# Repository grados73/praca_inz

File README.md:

# Praca Dyplomowa (inżynierska)
Tematem pracy była Analiza konstrukcyjna systemu śledzenia linii.

Zaawansowane rozwiązania techniczne pomagają w osiąganiu coraz to lepszych wyników w różnych dyscyplinach sportowych,
towarzyszą podczas treningów zapewniając wsparcie i umożliwiając pokonywanie kolejnych granic oraz realizację założonych celów.
Wspierają one nie tylko zawodowych sportowców, ale również amatorów, ze względu na ich ogólną dostępność. 
Coraz częściej spotkać można bardzo zaawansowane aplikacje i urządzenia, wykorzystywane w sporcie, 
a oferta firm zajmujących się produkcją takiego sprzętu nieustannie się poszerza o nowe rozwiązania.

Celem pracy była realizacja robota, wykorzystującego system śledzenia linii, w celu utrzymywania zadanego tempa biegacza trenującego na bieżni lekkoatletycznej, 
aby osiągnąć większą efektywność treningów. Projekt składa się z dwóch podzespołów. 
Pierwszy z nich jest niesiony przez biegacza, jego zadaniem jest pomiar tętna i utrzymanie go w zakresie ustalonym przez ćwiczącego. 
Drugi moduł ma za zadanie jechać po ustalonej linii i utrzymywać zadane tempo.

https://youtu.be/Zt6rl9LgnUI

Created by https://www.linkedin.com/in/kamil-gradowski-8706991aa - feel free to contact me! grados73

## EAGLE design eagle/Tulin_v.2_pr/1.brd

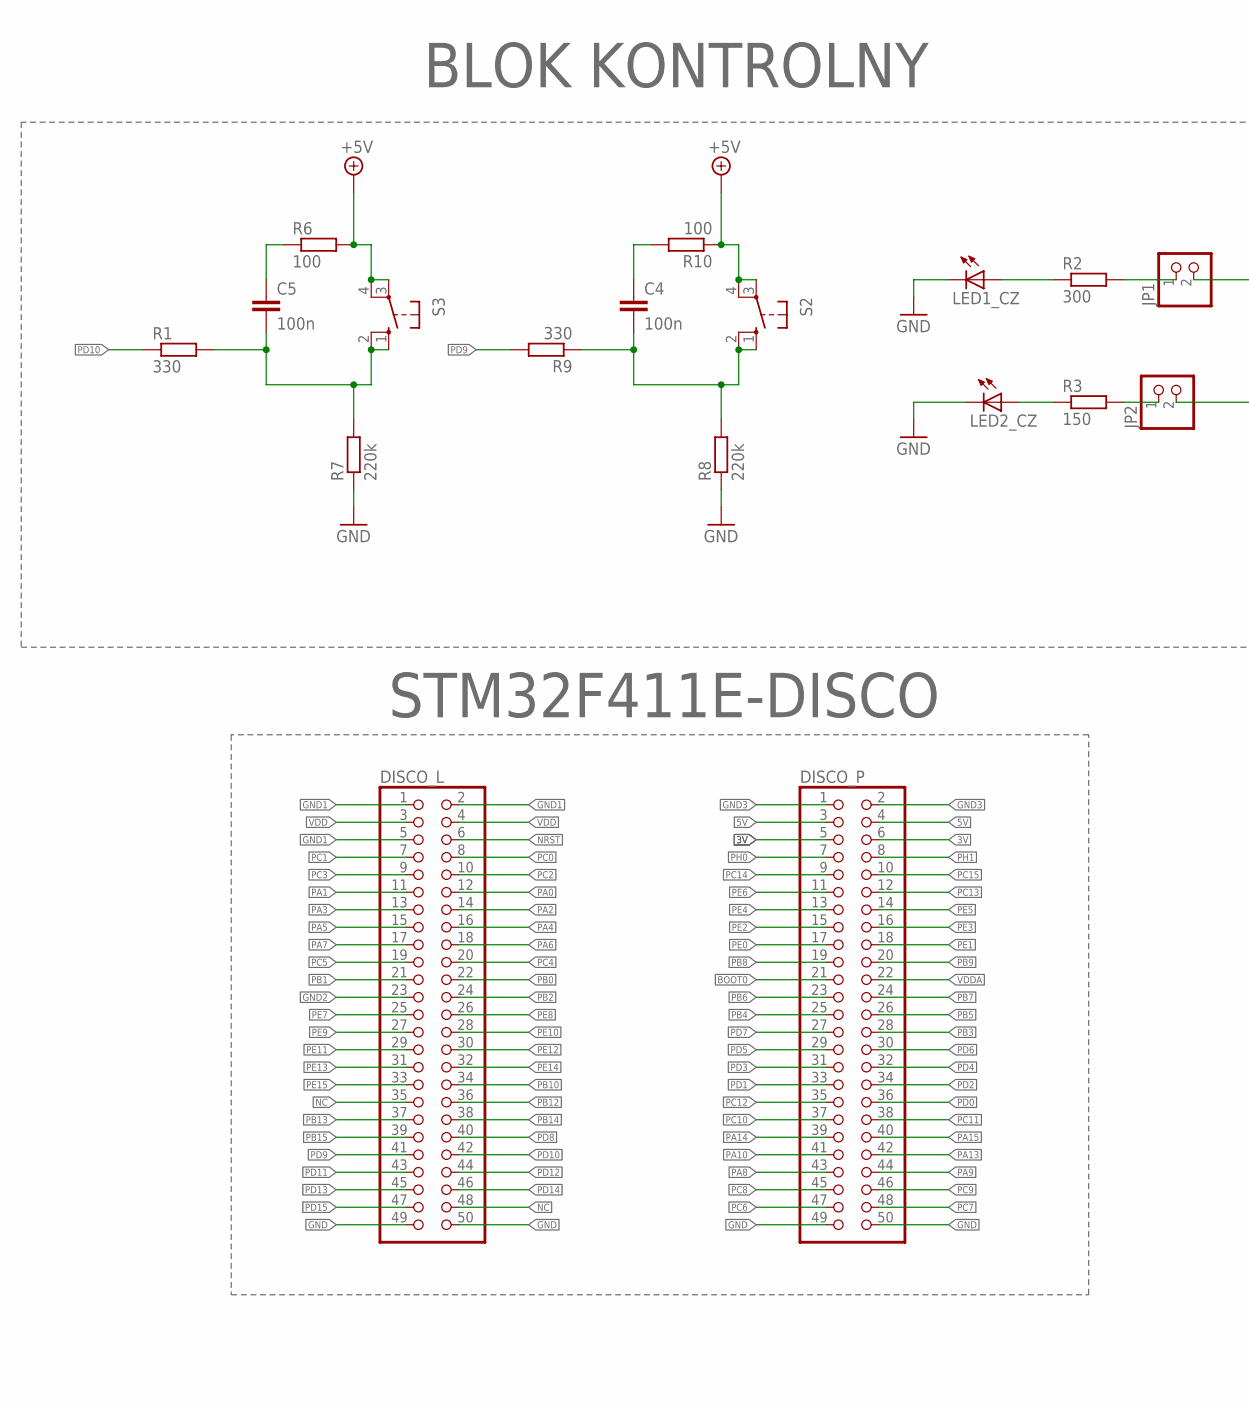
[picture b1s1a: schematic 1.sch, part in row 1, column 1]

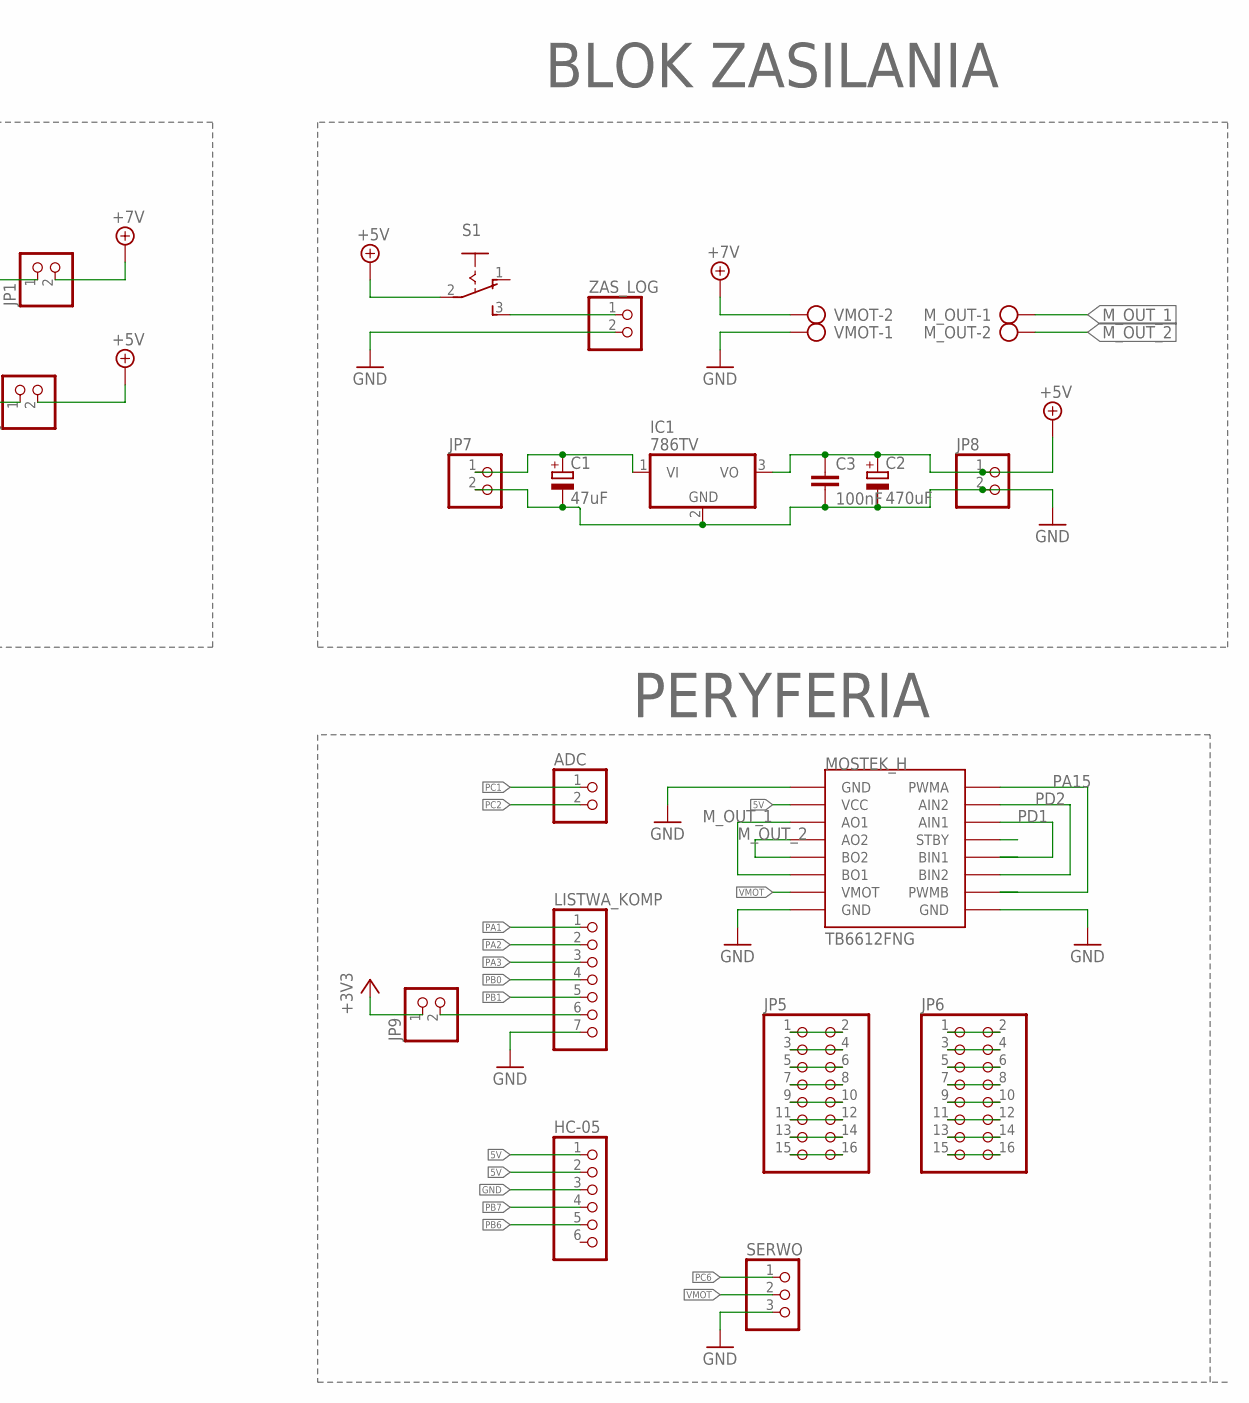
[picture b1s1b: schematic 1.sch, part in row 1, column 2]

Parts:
ADC: PINHD-1X2; 1X02
C1: 47uF; 153CLV-0405
C2: 470uF; 153CLV-0405
C3: 100nF; C025-024X044
C4, C5: 100n; C1206
DISCO_L: PINHD-2X25; 2X25
DISCO_P: PINHD-2X25; 2X25
HC-05: PINHD-1X6; 1X06
IC1: 786TV; TO220V
JP1, JP2, JP7, JP8, JP9: PINHD-1X2; 1X02
JP5, JP6: PINHD-2X8; 2X08
LED1_CZ, LED2_CZ: LEDSML1206; SML1206
LISTWA_KOMP: PINHD-1X7; 1X07
MOSTEK_H: MODUL_POLOLU
M_OUT: AK300/2
R1, R9: 330; R0805
R2: 300; R0805
R3: 150; R0805
R6, R10: 100; R0805
R7, R8: 220k; R0805
S1: 255SB
S2, S3: 10-XX; B3F-10XX
SERWO: PINHD-1X3; 1X03
VMOT: AK300/2
ZAS_LOG: PINHD-1X2/90; 1X02/90

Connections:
3V: DISCO_P.5, DISCO_P.6, JP9.1
5V: C2.+, C3.1, DISCO_P.3, DISCO_P.4, HC-05.1, HC-05.2, IC1.3 (VO), JP2.2, JP8.1, MOSTEK_H.VCC, R6.2, R10.1, S1.2, S2.3, S2.4 (P1), S3.3, S3.4 (P1)
A: JP9.2, LISTWA_KOMP.6
BOOT0: DISCO_P.21
GND: C1.-, C2.-, C3.2, DISCO_L.49, DISCO_L.50, DISCO_P.49, DISCO_P.50, HC-05.3, IC1.2 (GND), JP7.2, JP8.2, LED1_CZ.C, LED2_CZ.C, LISTWA_KOMP.7, MOSTEK_H.GND1 (GND), MOSTEK_H.GND2 (GND), MOSTEK_H.GND3 (GND), R7.1, R8.1, SERWO.3, VMOT.1, ZAS_LOG.2
GND1: DISCO_L.1, DISCO_L.2, DISCO_L.5
GND2: DISCO_L.23
GND3: DISCO_P.1, DISCO_P.2
M_OUT_1: MOSTEK_H.AO1, MOSTEK_H.BO1, M_OUT.1
M_OUT_2: MOSTEK_H.A02 (AO2), MOSTEK_H.BO2, M_OUT.2
unnamed: JP5.1, JP5.2
unnamed: JP5.3, JP5.4
unnamed: JP5.5, JP5.6
unnamed: JP5.7, JP5.8
unnamed: JP5.9, JP5.10
unnamed: JP5.11, JP5.12
unnamed: JP5.13, JP5.14
unnamed: JP5.15, JP5.16
unnamed: JP6.1, JP6.2
unnamed: JP6.3, JP6.4
unnamed: JP6.5, JP6.6
unnamed: JP6.7, JP6.8
unnamed: JP6.9, JP6.10
unnamed: JP6.11, JP6.12
unnamed: JP6.13, JP6.14
unnamed: JP6.15, JP6.16
unnamed: C1.+, IC1.1 (VI), JP7.1
unnamed: S1.3 (S), ZAS_LOG.1
unnamed: LED1_CZ.A, R2.1
unnamed: LED2_CZ.A, R3.1
unnamed: C4.2, R8.2, R9.1, S2.1 (S), S2.2 (S1)
unnamed: JP1.1, R2.2
unnamed: C5.2, R1.2, R7.2, S3.1 (S), S3.2 (S1)
unnamed: JP2.1, R3.2
unnamed: C4.1, R10.2
unnamed: C5.1, R6.1
NC: DISCO_L.35, DISCO_L.48
NRST: DISCO_L.6
PA0: DISCO_L.12
PA1: DISCO_L.11, LISTWA_KOMP.1
PA2: DISCO_L.14, LISTWA_KOMP.2
PA3: DISCO_L.13, LISTWA_KOMP.3
PA4: DISCO_L.16
PA5: DISCO_L.15
PA6: DISCO_L.18
PA7: DISCO_L.17
PA8: DISCO_P.43
PA9: DISCO_P.44
PA10: DISCO_P.41
PA13: DISCO_P.42
PA14: DISCO_P.39
PA15: DISCO_P.40, MOSTEK_H.PWMA, MOSTEK_H.PWMB
PB0: DISCO_L.22, LISTWA_KOMP.4
PB1: DISCO_L.21, LISTWA_KOMP.5
PB2: DISCO_L.24
PB3: DISCO_P.28
PB4: DISCO_P.25
PB5: DISCO_P.26
PB6: DISCO_P.23, HC-05.5
PB7: DISCO_P.24, HC-05.4
PB8: DISCO_P.19
PB9: DISCO_P.20
PB10: DISCO_L.34
PB12: DISCO_L.36
PB13: DISCO_L.37
PB14: DISCO_L.38
PB15: DISCO_L.39
PC0: DISCO_L.8
PC1: ADC.1, DISCO_L.7
PC2: ADC.2, DISCO_L.10
PC3: DISCO_L.9
PC4: DISCO_L.20
PC5: DISCO_L.19
PC6: DISCO_P.47, SERWO.1
PC7: DISCO_P.48
PC8: DISCO_P.45
PC9: DISCO_P.46
PC10: DISCO_P.37
PC11: DISCO_P.38
PC12: DISCO_P.35
PC13: DISCO_P.12
PC14: DISCO_P.9
PC15: DISCO_P.10
PD0: DISCO_P.36
PD1: DISCO_P.33, MOSTEK_H.AIN1, MOSTEK_H.BIN1
PD2: DISCO_P.34, MOSTEK_H.AIN2, MOSTEK_H.BIN2
PD3: DISCO_P.31
PD4: DISCO_P.32
PD5: DISCO_P.29
PD6: DISCO_P.30
PD7: DISCO_P.27
PD8: DISCO_L.40
PD9: DISCO_L.41, R9.2
PD10: DISCO_L.42, R1.1
PD11: DISCO_L.43
PD12: DISCO_L.44
PD13: DISCO_L.45
PD14: DISCO_L.46
PD15: DISCO_L.47
PE0: DISCO_P.17
PE1: DISCO_P.18
PE2: DISCO_P.15
PE3: DISCO_P.16
PE4: DISCO_P.13
PE5: DISCO_P.14
PE6: DISCO_P.11
PE7: DISCO_L.25
PE8: DISCO_L.26
PE9: DISCO_L.27
PE10: DISCO_L.28
PE11: DISCO_L.29
PE12: DISCO_L.30
PE13: DISCO_L.31
PE14: DISCO_L.32
PE15: DISCO_L.33
PH0: DISCO_P.7
PH1: DISCO_P.8
VDD: DISCO_L.3, DISCO_L.4
VDDA: DISCO_P.22
VMOT: JP1.2, MOSTEK_H.VMOT, SERWO.2, VMOT.2

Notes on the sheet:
BLOK ZASILANIA
BLOK KONTROLNY
STM32F411E-DISCO
PERYFERIA

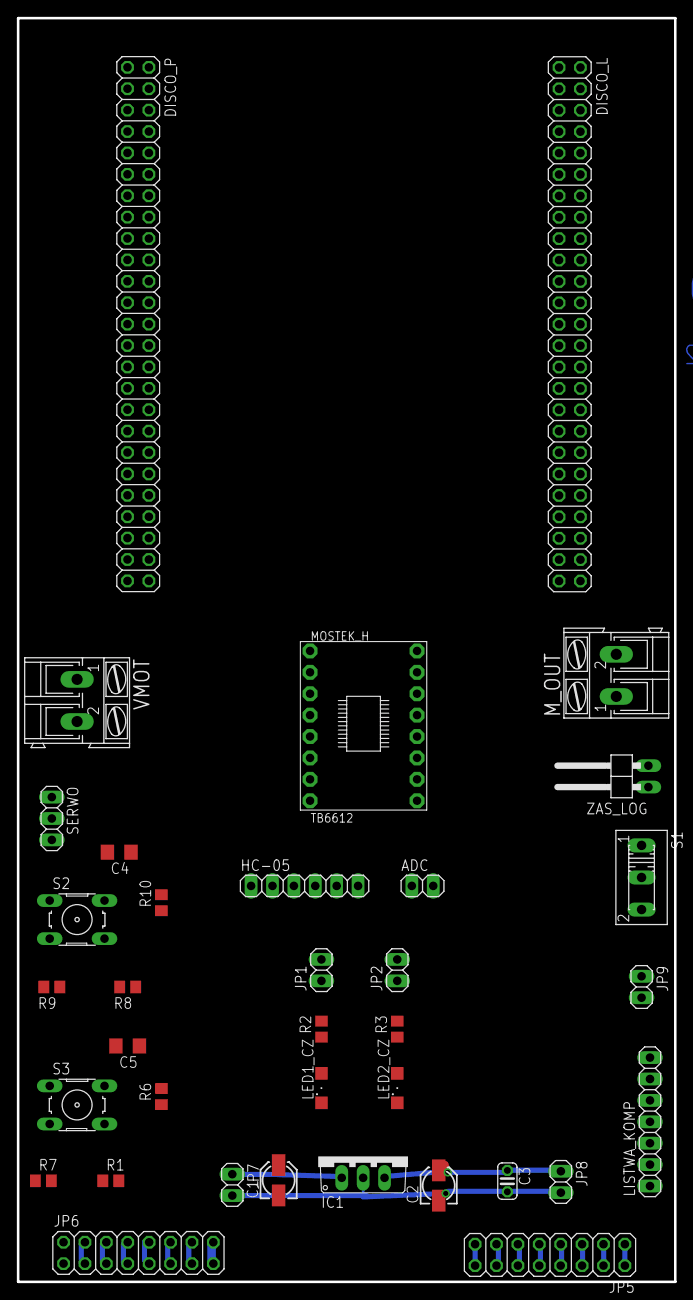
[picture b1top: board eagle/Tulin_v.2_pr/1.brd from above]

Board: 2 copper layers, 78.0 x 150.0 mm, 36 parts (0 on the bottom side), 52 nets.

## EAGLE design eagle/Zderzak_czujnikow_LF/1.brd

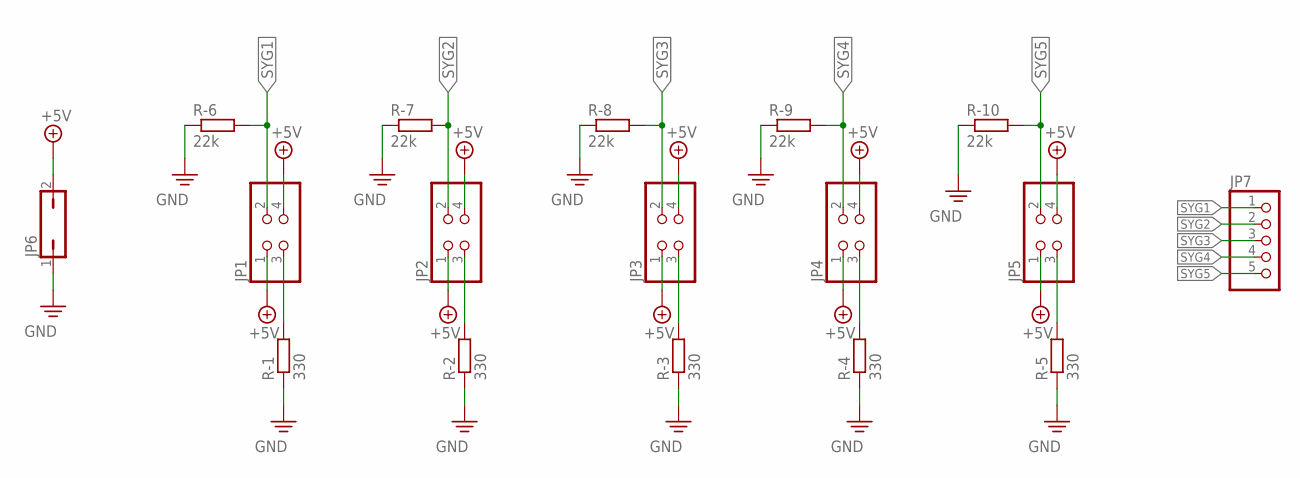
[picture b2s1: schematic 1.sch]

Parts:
JP1, JP2, JP3, JP4, JP5: PINHD-2X2; 2X02
JP6: JP1Q; JP1
JP7: PINHD-1X5; 1X05
R-1, R-2, R-3, R-4, R-5: 330; 0204/7
R-6, R-7, R-8, R-9, R-10: 22k; 0204/7

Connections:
+5V: JP1.1, JP1.4, JP2.1, JP2.4, JP3.1, JP3.4, JP4.1, JP4.4, JP5.1, JP5.4, JP6.2
unnamed: JP1.3, R-1.2
unnamed: JP2.3, R-2.2
unnamed: JP3.3, R-3.2
unnamed: JP4.3, R-4.2
unnamed: JP5.3, R-5.2
PE: JP6.1, R-1.1, R-2.1, R-3.1, R-4.1, R-5.1, R-6.1, R-7.1, R-8.1, R-9.1, R-10.1
SYG1: JP1.2, JP7.1, R-6.2
SYG2: JP2.2, JP7.2, R-7.2
SYG3: JP3.2, JP7.3, R-8.2
SYG4: JP4.2, JP7.4, R-9.2
SYG5: JP5.2, JP7.5, R-10.2

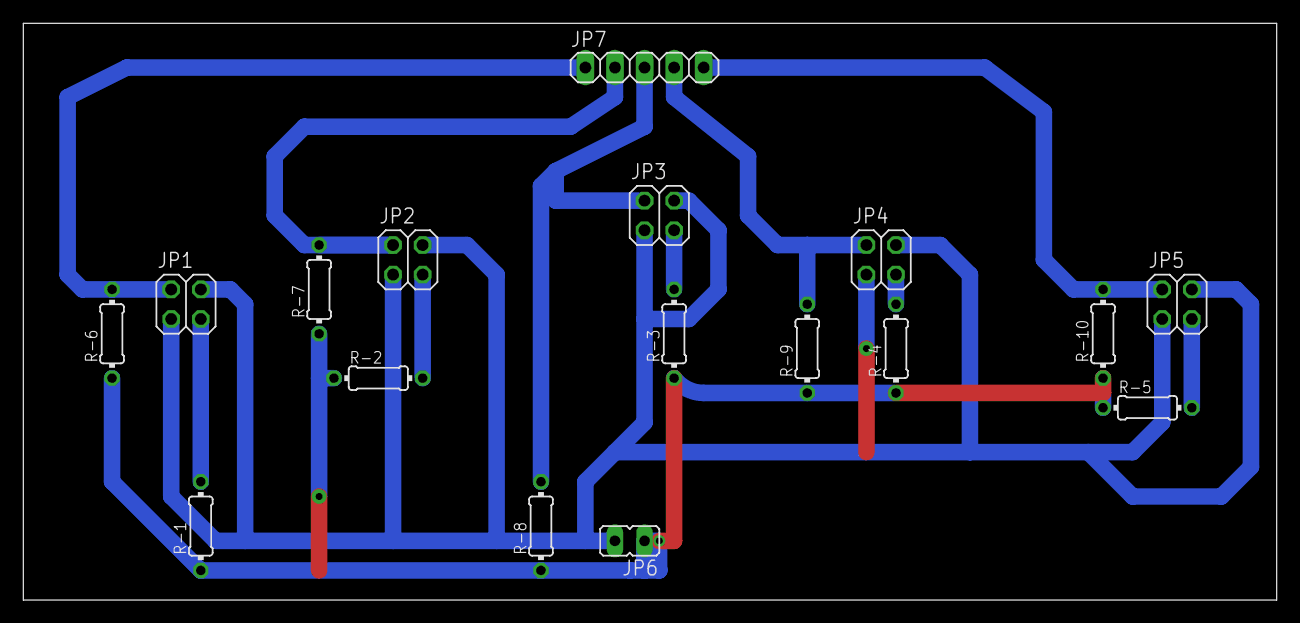
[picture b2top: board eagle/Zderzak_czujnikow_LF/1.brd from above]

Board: 2 copper layers, 107.6 x 49.5 mm, 17 parts (0 on the bottom side), 12 nets.

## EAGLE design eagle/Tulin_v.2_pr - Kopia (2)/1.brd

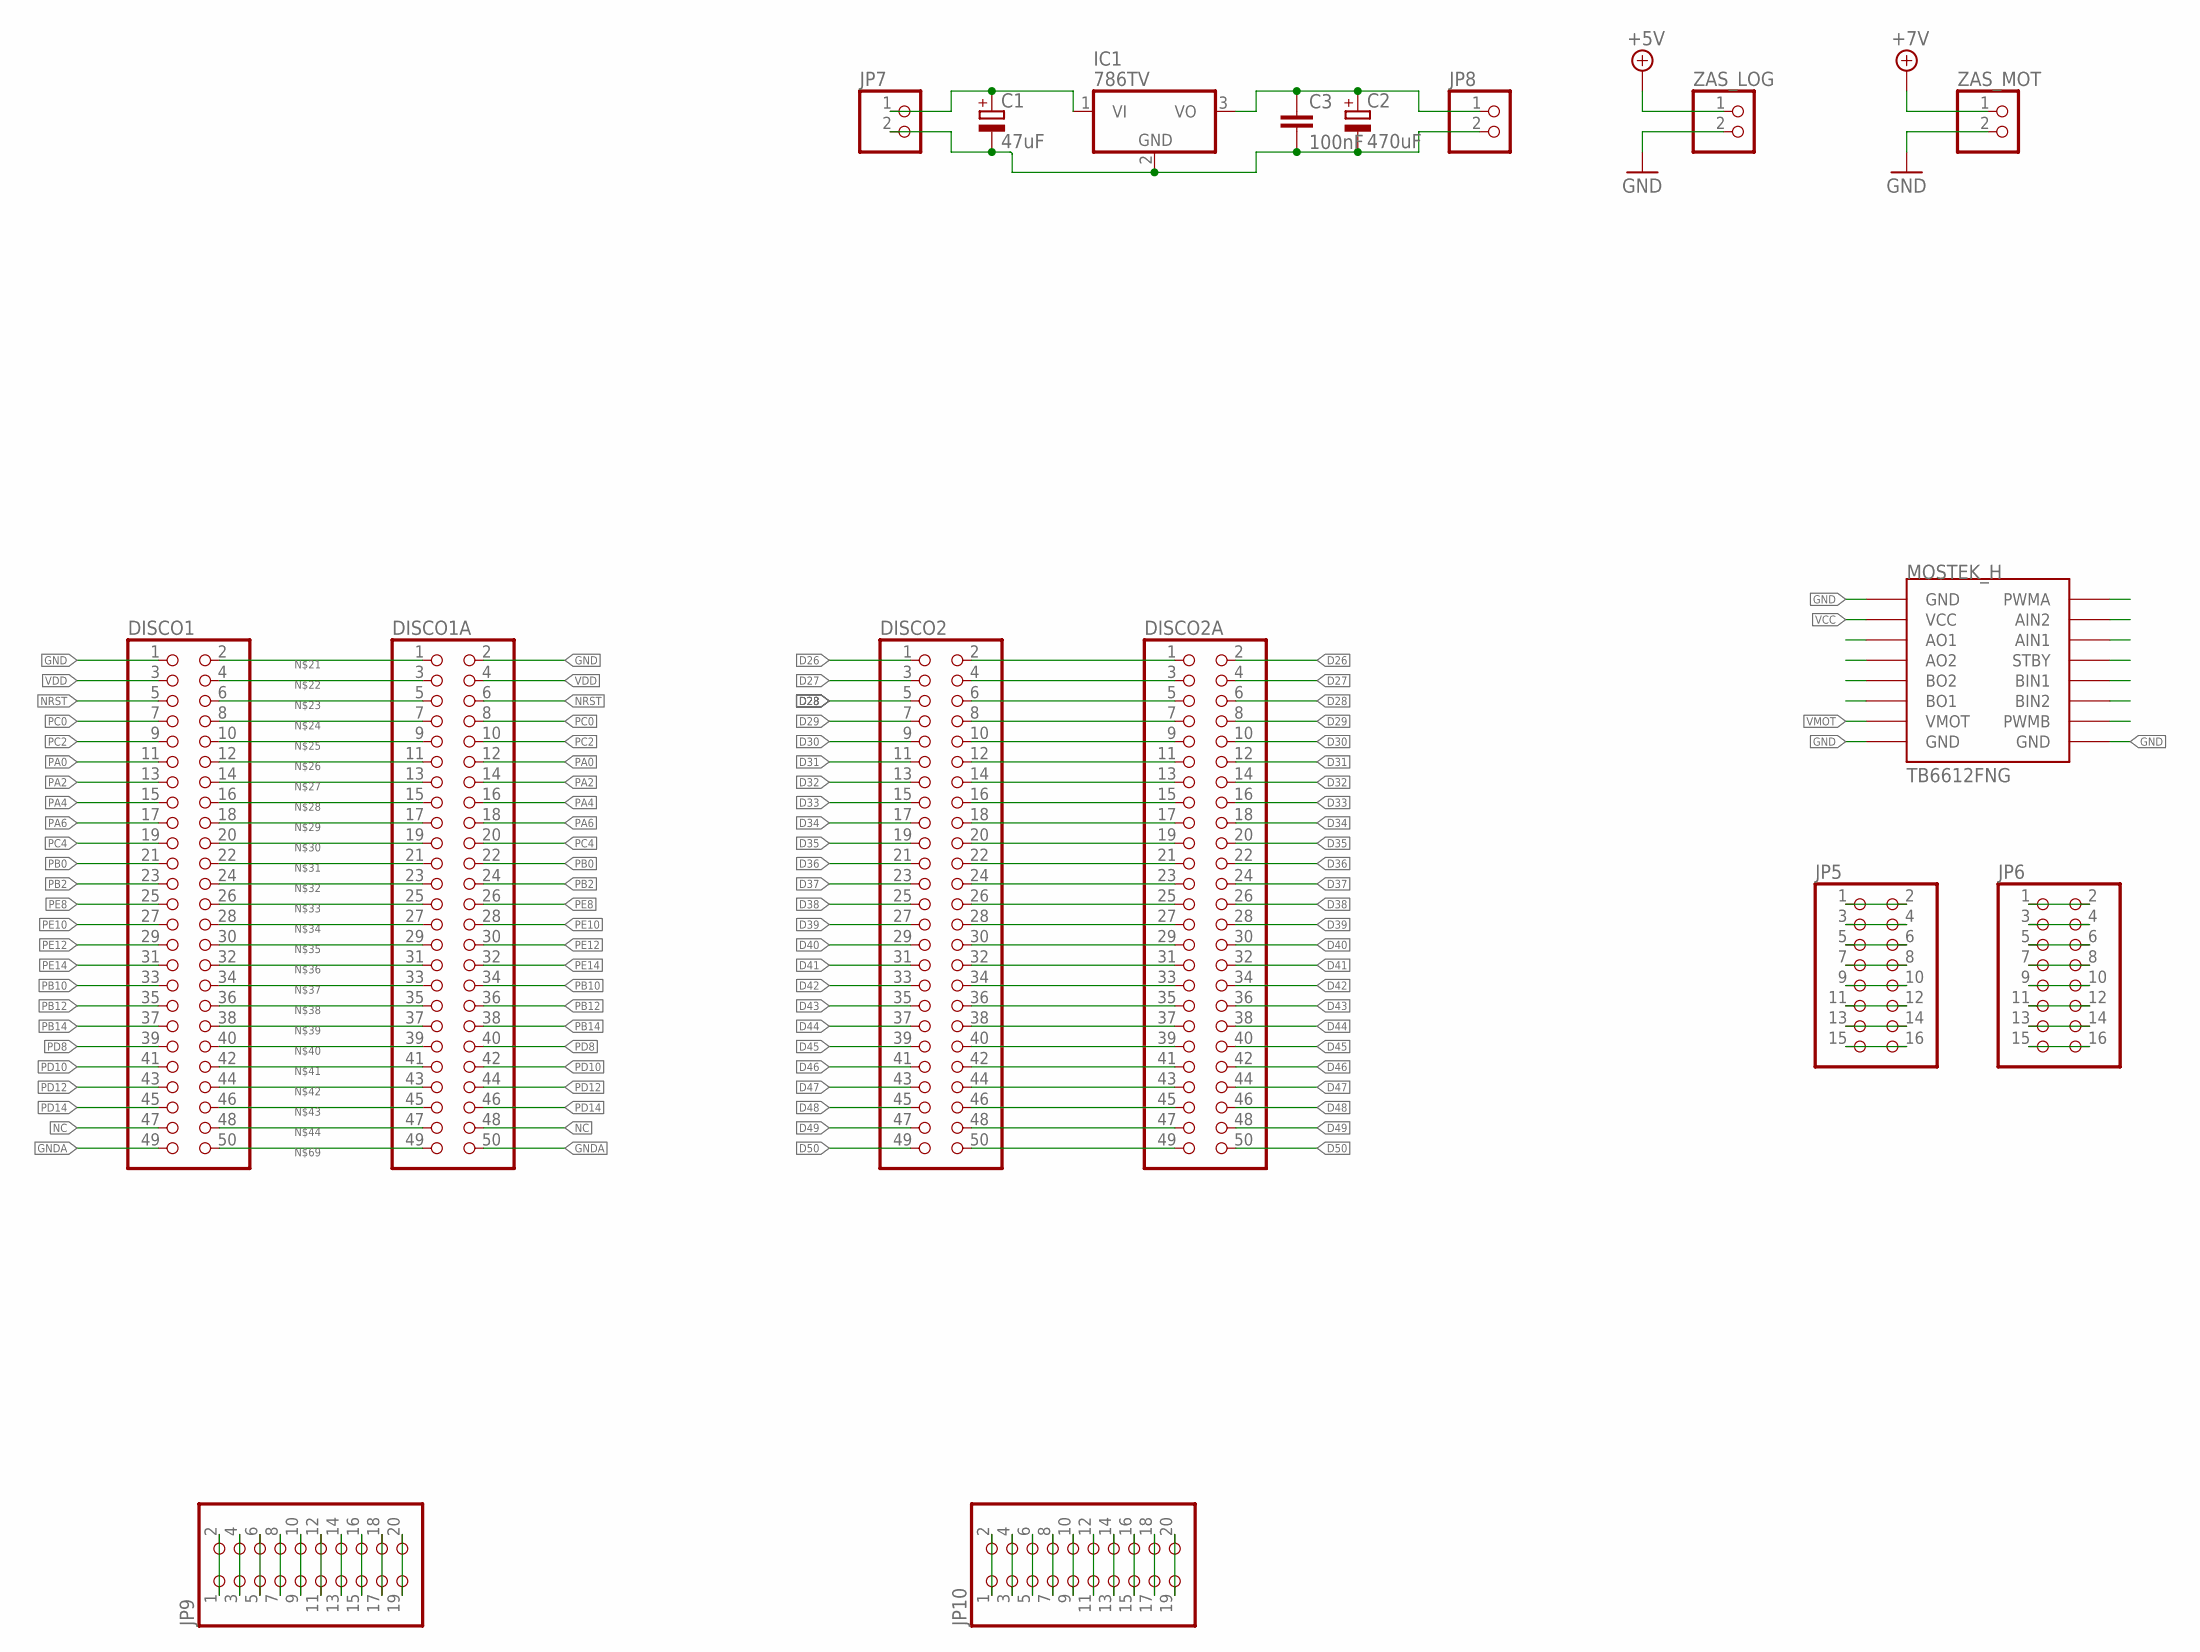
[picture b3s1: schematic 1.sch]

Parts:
C1: 47uF; 153CLV-0405
C2: 470uF; 153CLV-0405
C3: 100nF; C025-024X044
DISCO1, DISCO1A, DISCO2, DISCO2A: PINHD-2X25; 2X25
IC1: 786TV; TO220V
JP5, JP6: PINHD-2X8; 2X08
JP7, JP8: PINHD-1X2; 1X02
JP9, JP10: PINHD-2X10; 2X10
MOSTEK_H: MODUL_POLOLU
ZAS_LOG: PINHD-1X2/90; 1X02/90
ZAS_MOT: PINHD-1X2/90; 1X02/90

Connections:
+5V: ZAS_LOG.1
D26: DISCO2.1, DISCO2A.2
D27: DISCO2.3, DISCO2A.4
D28: DISCO2.5, DISCO2A.6
D29: DISCO2.7, DISCO2A.8
D30: DISCO2.9, DISCO2A.10
D31: DISCO2.11, DISCO2A.12
D32: DISCO2.13, DISCO2A.14
D33: DISCO2.15, DISCO2A.16
D34: DISCO2.17, DISCO2A.18
D35: DISCO2.19, DISCO2A.20
D36: DISCO2.21, DISCO2A.22
D37: DISCO2.23, DISCO2A.24
D38: DISCO2.25, DISCO2A.26
D39: DISCO2.27, DISCO2A.28
D40: DISCO2.29, DISCO2A.30
D41: DISCO2.31, DISCO2A.32
D42: DISCO2.33, DISCO2A.34
D43: DISCO2.35, DISCO2A.36
D44: DISCO2.37, DISCO2A.38
D45: DISCO2.39, DISCO2A.40
D46: DISCO2.41, DISCO2A.42
D47: DISCO2.43, DISCO2A.44
D48: DISCO2.45, DISCO2A.46
D49: DISCO2.47, DISCO2A.48
D50: DISCO2.49, DISCO2A.50
GND: DISCO1.1, DISCO1A.2, MOSTEK_H.GND1 (GND), MOSTEK_H.GND2 (GND), MOSTEK_H.GND3 (GND), ZAS_LOG.2, ZAS_MOT.2
GNDA: DISCO1.49, DISCO1A.50
unnamed: JP5.1, JP5.2
unnamed: JP5.3, JP5.4
unnamed: JP5.5, JP5.6
unnamed: JP5.7, JP5.8
unnamed: JP5.9, JP5.10
unnamed: JP5.11, JP5.12
unnamed: JP5.13, JP5.14
unnamed: JP5.15, JP5.16
unnamed: JP6.1, JP6.2
unnamed: JP6.3, JP6.4
unnamed: JP6.5, JP6.6
unnamed: JP6.7, JP6.8
unnamed: JP6.9, JP6.10
unnamed: JP6.11, JP6.12
unnamed: JP6.13, JP6.14
unnamed: JP6.15, JP6.16
unnamed: C1.+, IC1.1 (VI), JP7.1
unnamed: C2.+, C3.1, IC1.3 (VO), JP8.1
unnamed: C1.-, C2.-, C3.2, IC1.2 (GND), JP7.2, JP8.2
unnamed: DISCO1.2, DISCO1A.1
unnamed: DISCO1.4, DISCO1A.3
unnamed: DISCO1.6, DISCO1A.5
unnamed: DISCO1.8, DISCO1A.7
unnamed: DISCO1.10, DISCO1A.9
unnamed: DISCO1.12, DISCO1A.11
unnamed: DISCO1.14, DISCO1A.13
unnamed: DISCO1.16, DISCO1A.15
unnamed: DISCO1.18, DISCO1A.17
unnamed: DISCO1.20, DISCO1A.19
unnamed: DISCO1.22, DISCO1A.21
unnamed: DISCO1.24, DISCO1A.23
unnamed: DISCO1.26, DISCO1A.25
unnamed: DISCO1.28, DISCO1A.27
unnamed: DISCO1.30, DISCO1A.29
unnamed: DISCO1.32, DISCO1A.31
unnamed: DISCO1.34, DISCO1A.33
unnamed: DISCO1.36, DISCO1A.35
unnamed: DISCO1.38, DISCO1A.37
unnamed: DISCO1.40, DISCO1A.39
unnamed: DISCO1.42, DISCO1A.41
unnamed: DISCO1.44, DISCO1A.43
unnamed: DISCO1.46, DISCO1A.45
unnamed: DISCO1.48, DISCO1A.47
unnamed: DISCO1.50, DISCO1A.49
unnamed: DISCO2.2, DISCO2A.1
unnamed: DISCO2.4, DISCO2A.3
unnamed: DISCO2.6, DISCO2A.5
unnamed: DISCO2.8, DISCO2A.7
unnamed: DISCO2.10, DISCO2A.9
unnamed: DISCO2.12, DISCO2A.11
unnamed: DISCO2.14, DISCO2A.13
unnamed: DISCO2.16, DISCO2A.15
unnamed: DISCO2.18, DISCO2A.17
unnamed: DISCO2.20, DISCO2A.19
unnamed: DISCO2.22, DISCO2A.21
unnamed: DISCO2.24, DISCO2A.23
unnamed: DISCO2.26, DISCO2A.25
unnamed: DISCO2.28, DISCO2A.27
unnamed: DISCO2.30, DISCO2A.29
unnamed: DISCO2.32, DISCO2A.31
unnamed: DISCO2.34, DISCO2A.33
unnamed: DISCO2.36, DISCO2A.35
unnamed: DISCO2.38, DISCO2A.37
unnamed: DISCO2.40, DISCO2A.39
unnamed: DISCO2.42, DISCO2A.41
unnamed: DISCO2.44, DISCO2A.43
unnamed: DISCO2.46, DISCO2A.45
unnamed: DISCO2.48, DISCO2A.47
unnamed: DISCO2.50, DISCO2A.49
unnamed: JP9.1, JP9.2
unnamed: JP9.3, JP9.4
unnamed: JP9.5, JP9.6
unnamed: JP9.7, JP9.8
unnamed: JP9.9, JP9.10
unnamed: JP9.11, JP9.12
unnamed: JP9.13, JP9.14
unnamed: JP9.15, JP9.16
unnamed: JP9.17, JP9.18
unnamed: JP9.19, JP9.20
unnamed: JP10.1, JP10.2
unnamed: JP10.3, JP10.4
unnamed: JP10.5, JP10.6
unnamed: JP10.7, JP10.8
unnamed: JP10.9, JP10.10
unnamed: JP10.11, JP10.12
unnamed: JP10.13, JP10.14
unnamed: JP10.15, JP10.16
unnamed: JP10.17, JP10.18
unnamed: JP10.19, JP10.20
NC: DISCO1.47, DISCO1A.48
NRST: DISCO1.5, DISCO1A.6
PA0: DISCO1.11, DISCO1A.12
PA2: DISCO1.13, DISCO1A.14
PA4: DISCO1.15, DISCO1A.16
PA6: DISCO1.17, DISCO1A.18
PB0: DISCO1.21, DISCO1A.22
PB2: DISCO1.23, DISCO1A.24
PB10: DISCO1.33, DISCO1A.34
PB12: DISCO1.35, DISCO1A.36
PB14: DISCO1.37, DISCO1A.38
PC0: DISCO1.7, DISCO1A.8
PC2: DISCO1.9, DISCO1A.10
PC4: DISCO1.19, DISCO1A.20
PD8: DISCO1.39, DISCO1A.40
PD10: DISCO1.41, DISCO1A.42
PD12: DISCO1.43, DISCO1A.44
PD14: DISCO1.45, DISCO1A.46
PE8: DISCO1.25, DISCO1A.26
PE10: DISCO1.27, DISCO1A.28
PE12: DISCO1.29, DISCO1A.30
PE14: DISCO1.31, DISCO1A.32
VCC: MOSTEK_H.VCC
VDD: DISCO1.3, DISCO1A.4
VMOT: MOSTEK_H.VMOT, ZAS_MOT.1

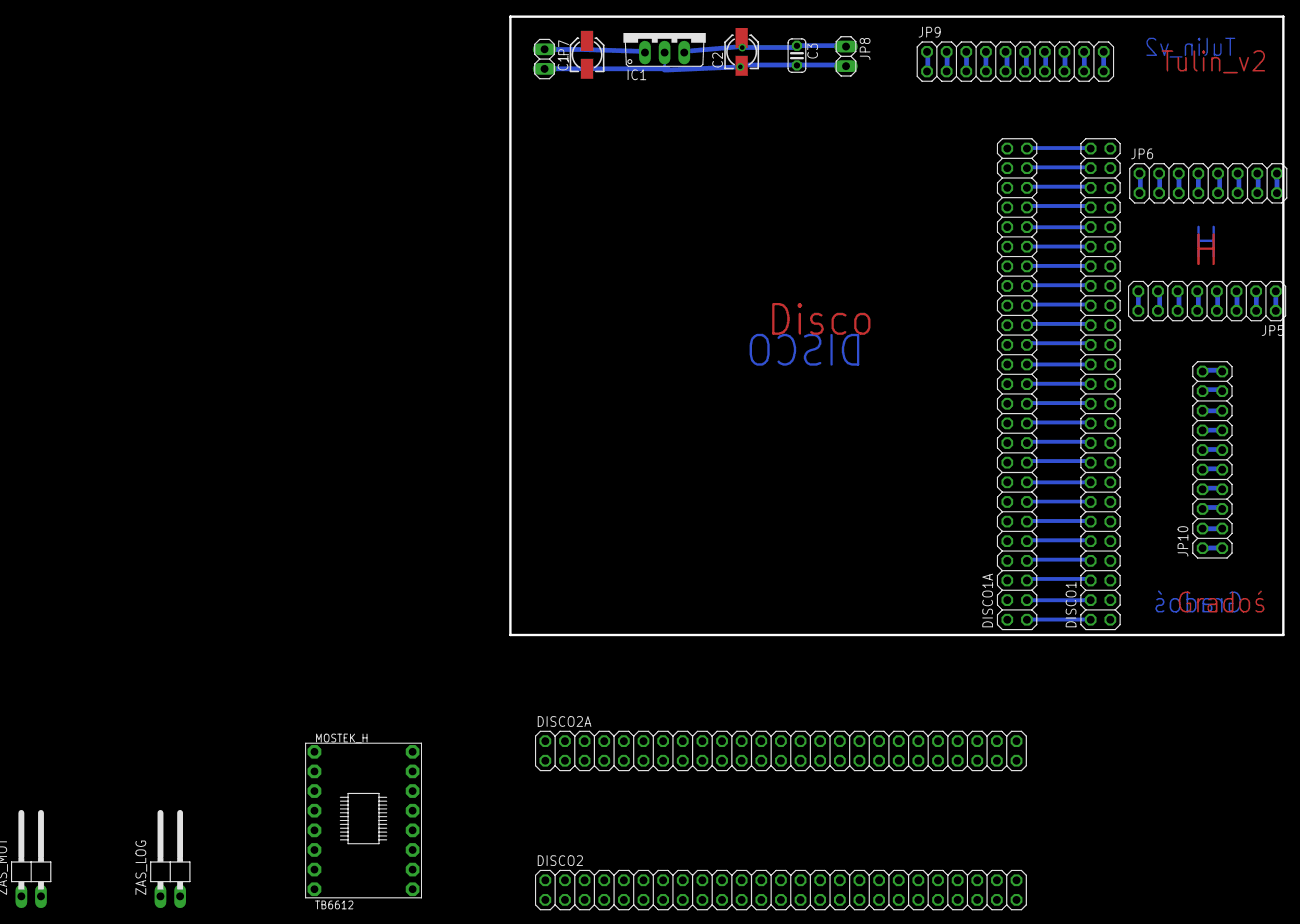
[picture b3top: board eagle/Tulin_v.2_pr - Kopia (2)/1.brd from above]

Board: 2 copper layers, 100.0 x 80.0 mm, 17 parts (0 on the bottom side), 140 nets.

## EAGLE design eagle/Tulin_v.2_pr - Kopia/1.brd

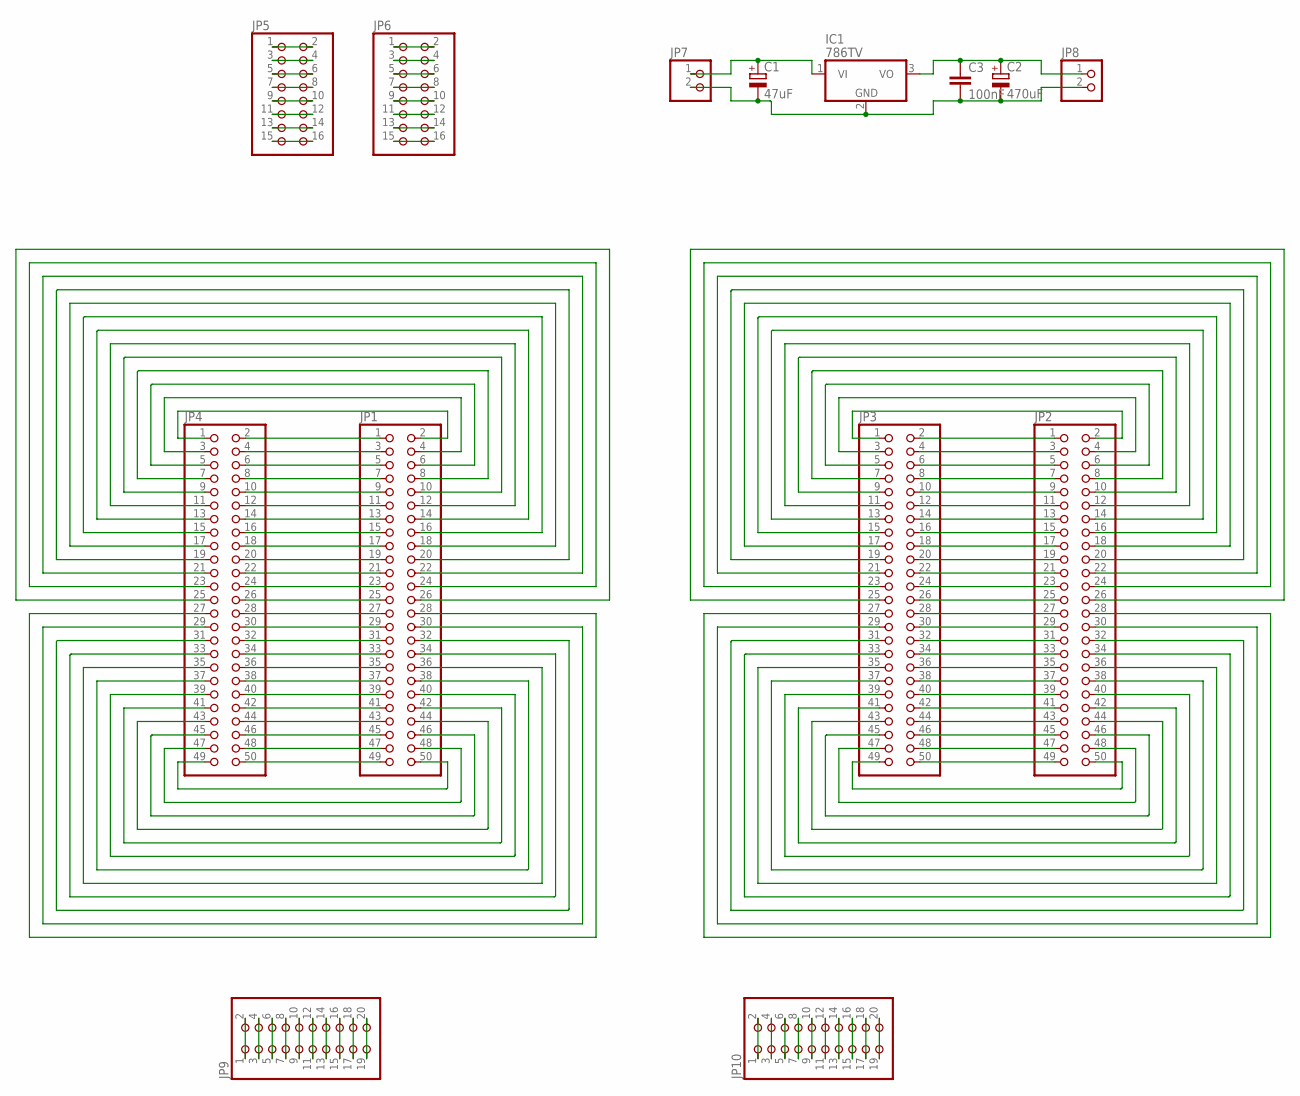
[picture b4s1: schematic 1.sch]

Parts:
C1: 47uF; 153CLV-0405
C2: 470uF; 153CLV-0405
C3: 100nF; C025-024X044
IC1: 786TV; TO220V
JP1, JP2, JP3, JP4: PINHD-2X25; 2X25
JP5, JP6: PINHD-2X8; 2X08
JP7, JP8: PINHD-1X2; 1X02
JP9, JP10: PINHD-2X10; 2X10

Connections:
unnamed: JP5.1, JP5.2
unnamed: JP5.3, JP5.4
unnamed: JP5.5, JP5.6
unnamed: JP5.7, JP5.8
unnamed: JP5.9, JP5.10
unnamed: JP5.11, JP5.12
unnamed: JP5.13, JP5.14
unnamed: JP5.15, JP5.16
unnamed: JP6.1, JP6.2
unnamed: JP6.3, JP6.4
unnamed: JP6.5, JP6.6
unnamed: JP6.7, JP6.8
unnamed: JP6.9, JP6.10
unnamed: JP6.11, JP6.12
unnamed: JP6.13, JP6.14
unnamed: JP6.15, JP6.16
unnamed: C1.+, IC1.1 (VI), JP7.1
unnamed: C2.+, C3.1, IC1.3 (VO), JP8.1
unnamed: C1.-, C2.-, C3.2, IC1.2 (GND), JP7.2, JP8.2
unnamed: JP1.2, JP4.1
unnamed: JP1.1, JP4.2
unnamed: JP1.3, JP4.4
unnamed: JP1.5, JP4.6
unnamed: JP1.7, JP4.8
unnamed: JP1.9, JP4.10
unnamed: JP1.11, JP4.12
unnamed: JP1.13, JP4.14
unnamed: JP1.15, JP4.16
unnamed: JP1.17, JP4.18
unnamed: JP1.19, JP4.20
unnamed: JP1.21, JP4.22
unnamed: JP1.23, JP4.24
unnamed: JP1.25, JP4.26
unnamed: JP1.27, JP4.28
unnamed: JP1.29, JP4.30
unnamed: JP1.31, JP4.32
unnamed: JP1.33, JP4.34
unnamed: JP1.35, JP4.36
unnamed: JP1.37, JP4.38
unnamed: JP1.39, JP4.40
unnamed: JP1.41, JP4.42
unnamed: JP1.43, JP4.44
unnamed: JP1.45, JP4.46
unnamed: JP1.47, JP4.48
unnamed: JP1.4, JP4.3
unnamed: JP1.6, JP4.5
unnamed: JP1.8, JP4.7
unnamed: JP1.10, JP4.9
unnamed: JP1.12, JP4.11
unnamed: JP1.14, JP4.13
unnamed: JP1.16, JP4.15
unnamed: JP1.18, JP4.17
unnamed: JP1.20, JP4.19
unnamed: JP1.22, JP4.21
unnamed: JP1.24, JP4.23
unnamed: JP1.26, JP4.25
unnamed: JP1.50, JP4.49
unnamed: JP1.48, JP4.47
unnamed: JP1.46, JP4.45
unnamed: JP1.44, JP4.43
unnamed: JP1.42, JP4.41
unnamed: JP1.40, JP4.39
unnamed: JP1.38, JP4.37
unnamed: JP1.36, JP4.35
unnamed: JP1.34, JP4.33
unnamed: JP1.32, JP4.31
unnamed: JP1.30, JP4.29
unnamed: JP1.28, JP4.27
unnamed: JP1.49, JP4.50
unnamed: JP2.1, JP3.2
unnamed: JP2.3, JP3.4
unnamed: JP2.5, JP3.6
unnamed: JP2.7, JP3.8
unnamed: JP2.9, JP3.10
unnamed: JP2.11, JP3.12
unnamed: JP2.13, JP3.14
unnamed: JP2.15, JP3.16
unnamed: JP2.17, JP3.18
unnamed: JP2.19, JP3.20
unnamed: JP2.21, JP3.22
unnamed: JP2.23, JP3.24
unnamed: JP2.25, JP3.26
unnamed: JP2.27, JP3.28
unnamed: JP2.29, JP3.30
unnamed: JP2.31, JP3.32
unnamed: JP2.33, JP3.34
unnamed: JP2.35, JP3.36
unnamed: JP2.37, JP3.38
unnamed: JP2.39, JP3.40
unnamed: JP2.41, JP3.42
unnamed: JP2.43, JP3.44
unnamed: JP2.45, JP3.46
unnamed: JP2.47, JP3.48
unnamed: JP2.2, JP3.1
unnamed: JP2.4, JP3.3
unnamed: JP2.6, JP3.5
unnamed: JP2.8, JP3.7
unnamed: JP2.10, JP3.9
unnamed: JP2.12, JP3.11
unnamed: JP2.14, JP3.13
unnamed: JP2.16, JP3.15
unnamed: JP2.18, JP3.17
unnamed: JP2.20, JP3.19
unnamed: JP2.22, JP3.21
unnamed: JP2.24, JP3.23
unnamed: JP2.26, JP3.25
unnamed: JP2.50, JP3.49
unnamed: JP2.48, JP3.47
unnamed: JP2.46, JP3.45
unnamed: JP2.44, JP3.43
unnamed: JP2.42, JP3.41
unnamed: JP2.40, JP3.39
unnamed: JP2.38, JP3.37
unnamed: JP2.36, JP3.35
unnamed: JP2.34, JP3.33
unnamed: JP2.32, JP3.31
unnamed: JP2.30, JP3.29
unnamed: JP2.28, JP3.27
unnamed: JP2.49, JP3.50
unnamed: JP9.1, JP9.2
unnamed: JP9.3, JP9.4
unnamed: JP9.5, JP9.6
unnamed: JP9.7, JP9.8
unnamed: JP9.9, JP9.10
unnamed: JP9.11, JP9.12
unnamed: JP9.13, JP9.14
unnamed: JP9.15, JP9.16
unnamed: JP9.17, JP9.18
unnamed: JP9.19, JP9.20
unnamed: JP10.1, JP10.2
unnamed: JP10.3, JP10.4
unnamed: JP10.5, JP10.6
unnamed: JP10.7, JP10.8
unnamed: JP10.9, JP10.10
unnamed: JP10.11, JP10.12
unnamed: JP10.13, JP10.14
unnamed: JP10.15, JP10.16
unnamed: JP10.17, JP10.18
unnamed: JP10.19, JP10.20

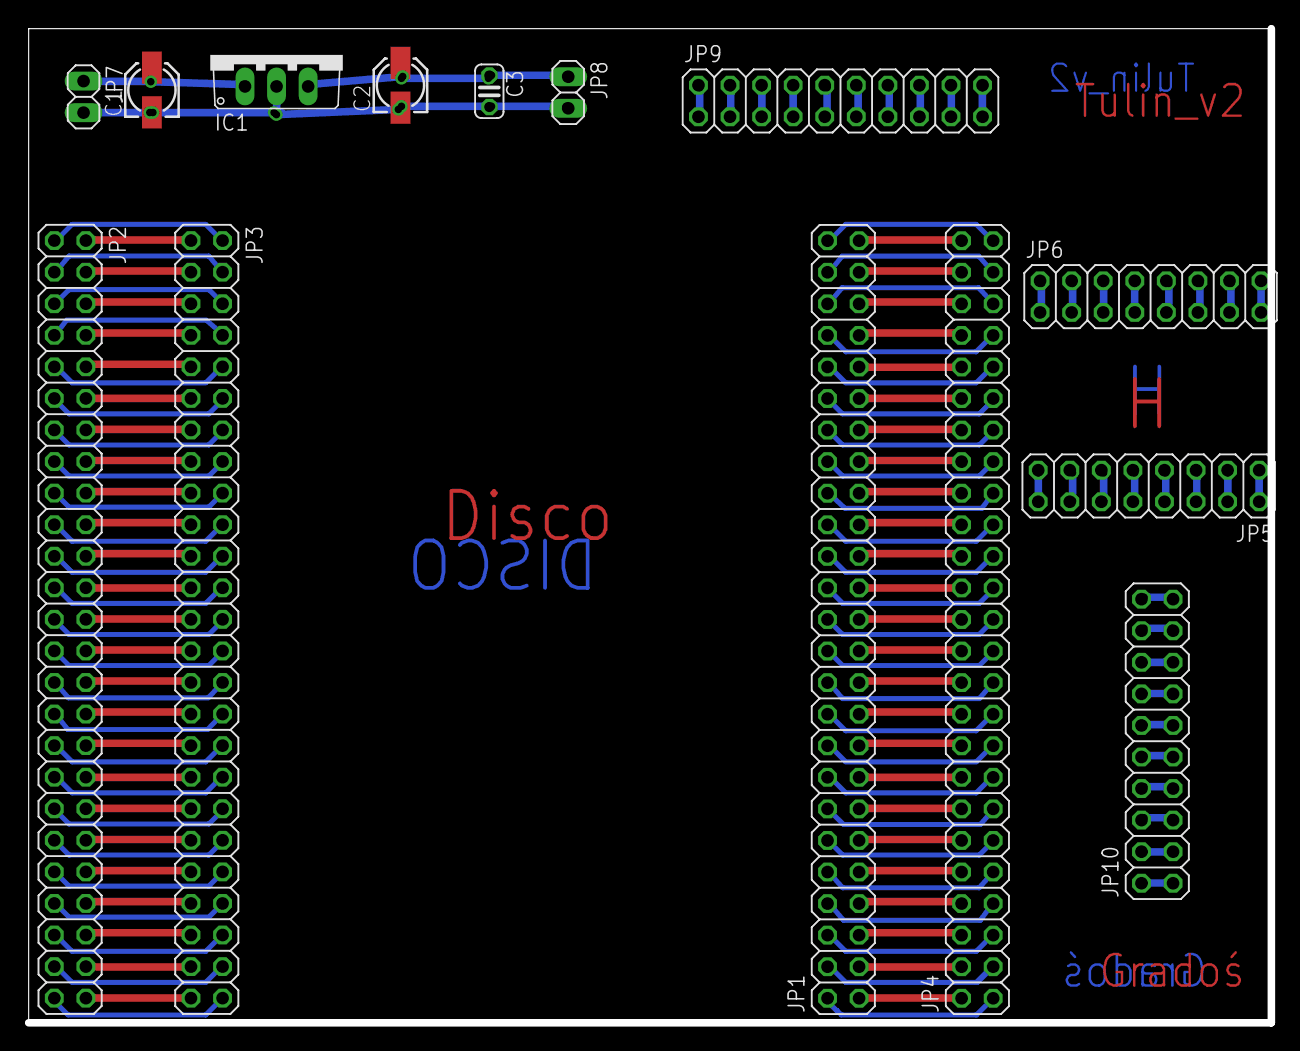
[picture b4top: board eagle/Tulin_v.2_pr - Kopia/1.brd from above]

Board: 2 copper layers, 100.0 x 80.0 mm, 14 parts (0 on the bottom side), 139 nets.

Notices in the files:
Nucleo_czerwy/01_Tulin_nucleo/Src/stm32f4xx_hal_msp.c:
COPYRIGHT(c) 2018 STMicroelectronics
(C) COPYRIGHT STMicroelectronics *****END OF FILE
Tulin_01_NEW/Src/stm32f4xx_hal_msp.c:
COPYRIGHT(c) 2017 STMicroelectronics
parts and their libraries:
SparkFun-IC-Microcontroller: Licensing: Creative Commons ShareAlike 4.0 International - https://creativecommons.org/licenses/by-sa/4.0
